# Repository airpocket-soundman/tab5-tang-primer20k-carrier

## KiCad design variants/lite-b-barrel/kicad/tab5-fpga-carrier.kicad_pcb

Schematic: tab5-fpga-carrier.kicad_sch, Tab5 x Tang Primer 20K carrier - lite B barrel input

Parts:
C1: 100u/35V; CP_Elec_6.3x7.7; LCSC C2983388
C3: 10n; C_0603_1608Metric; LCSC C57112
C4, C5: 10u/50V; C_1206_3216Metric; LCSC C13585
C6: 100n/50V; C_0603_1608Metric; LCSC C14663
C7: 220u/10V POSCAP; CP_EIA-7343-40_Kemet-Y; LCSC C242173
C8, C9: 47u/10V; C_1206_3216Metric; LCSC C96123; not fitted
C10: 10u/16V; C_1206_3216Metric; LCSC C13585
C11: 22u/10V; C_1206_3216Metric; LCSC C12891
C12, C13, C14, C15, C16, C17, C18, C19: 100n; C_0402_1005Metric; LCSC C1525
C20, C21, C22, C23, C24: 100n; C_0603_1608Metric; LCSC C14663
D1, D4: SS54; D_SMA; LCSC C22452
D3: SMBJ15A; D_SMB; LCSC C699013
D5, D6, D7, D8: LED; LED_0603_1608Metric; LCSC C2286
F1: PTC 3A hold; Fuse_1812_4532Metric; LCSC C47002391
F2: PTC 500mA; Fuse_1206_3216Metric; LCSC C315893
H3, H4, H5, H6: M3; MountingHole_3.2mm_M3
J1: DC 12V ONLY; BarrelJack_Horizontal
J3: M5-BUS (to Tab5); PinHeader_2x15_Tab5_Bottom
J4: SOCKET XDAP-4042044-20401; DDR3_XDAP_4042044_20401; LCSC C22471982
J5: HDMI OUT; HDMI_A_Molex_208658-1001_Horizontal
J6: PMOD1; PinHeader_2x06_P2.54mm_Vertical; not fitted
J7: PMOD2; PinHeader_2x06_P2.54mm_Vertical; not fitted
J8: GPIO pads; PinHeader_1x09_P2.54mm_Vertical; not fitted
JP1: BUS ARM (open by default); PinHeader_1x02_P2.54mm_Vertical
L1: 15u MS1040-150M; L_COILMX_MS1040; LCSC C380054
Q1, Q2, Q3, Q4: 2N7002; SOT-23; LCSC C8545
Q5: MMBT3904; SOT-23; LCSC C20526
R6, R36, R37, R52: 10k; R_0603_1608Metric; LCSC C25804
R7: 3.3k; R_0603_1608Metric; LCSC C22978
R8, R41, R47, R48, R49, R50: 100k; R_0603_1608Metric; LCSC C25803
R9: 15k; R_0603_1608Metric; LCSC C22809
R10, R11, R12, R13, R14, R15, R16, R19, R20, R21, R22, R23, R24, R26, R27: 680R; R_0603_1608Metric; LCSC C23228
R17, R18, R25: 0R; R_0603_1608Metric; LCSC C21189; not fitted
R28, R29, R32, R33, R34, R35: 510R; R_0603_1608Metric; LCSC C23193
R30, R31: 510R; R_0402_1005Metric; LCSC C25123
R38, R39: 2.2k; R_0603_1608Metric; LCSC C4190
R40, R51: 47k; R_0603_1608Metric; LCSC C25819
R42, R43, R44, R45: 1k; R_0603_1608Metric; LCSC C21190
R46: 22k; R_0603_1608Metric; LCSC C31850
SW1: SW; SW_SPST_EVQP0
SW2: RESET (Tab5); SW_SPST_EVQP0
SW3: FPGA ON/OFF; SW_DIP_SPSTx01_Slide_9.78x4.72mm_W7.62mm_P2.54mm
U2: TPS5430DDAR; TI_SO-PowerPAD-8_ThermalVias; LCSC C9864
U3: XC6206P332MR-G; SOT-23; LCSC C5446
U4, U5, U6: RCLAMP0524P; DFN2510-10L_RCLAMP0524P; LCSC C293965
U7, U8: SN74CB3Q3245PWR; TSSOP-20_4.4x6.5mm_P0.65mm; LCSC C470961
U9: TPS3839G33DBZR; SOT-23; LCSC C485802
U10: TPS3839K50DBZR; SOT-23; LCSC C702204

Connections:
+3V3: C11.1, C20.1, C21.1, J6.11, J6.12, J7.11, J7.12, J8.1, Q1.1 (G), Q2.1 (G), R36.1, R37.1, R46.1, R51.1, U3.2 (VO), U7.20 (VCC), U8.20 (VCC)
+5V: C7.1, C8.1, C9.1, C10.1, C23.1, F2.1, J4.4 (+5V), J4.5 (+5V), J4.6 (+5V), J4.7 (+5V), L1.2, R6.1, U3.3 (VI), U10.3 (VDD)
BUCK_BOOT: C3.1, U2.1 (BOOT)
BUCK_EN: R8.2, R9.1, SW3.1, U2.5 (EN)
BUCK_FB: R6.2, R7.1, R49.1, U2.4 (VSENSE)
BUCK_PH: C3.2, D4.1 (K), L1.1, U2.8 (PH)
BUS_ARM: JP1.2, Q3.1 (G), R47.1
BUS_OE_MID: Q3.2 (S), Q4.3 (D)
BUS_OE_N: Q3.3 (D), R46.2, U7.19 (~OE), U8.19 (~OE)
CORE_PGOOD: Q4.1 (G), R48.1, U10.2 (~RESET)
DC_IN: D1.2 (A), F1.2
DC_RAW: F1.1, J1.1
FB_TRIM: R49.2, R50.1
F_AUX0: J4.73 (F_AUX0), R11.2
F_AUX1: J4.79 (F_AUX1), R14.2
F_AUX2: J4.95 (F_AUX2), R19.2
F_AUX3: J4.97 (F_AUX3), R20.2
F_BTN0: J4.74 (F_BTN0), SW1.1
F_CLK: J4.52 (F_CLK), R10.2
F_D0: J4.77 (F_D0), R13.2
F_D1: J4.83 (F_D1), R15.2
F_D2: J4.85 (F_D2), R16.2
F_D3: J4.103 (F_D3), R22.2
F_D4: J4.101 (F_D4), R21.2
F_D5: J4.109 (F_D5), R24.2
F_D6: J4.107 (F_D6), R23.2
F_D7: J4.115 (F_D7), R26.2
F_DIR: J4.119 (F_DIR), R27.2
F_EXT35: J4.113 (F_EXT35), R25.2
F_EXT37: J4.89 (F_EXT37), R17.2
F_EXT38: J4.91 (F_EXT38), R18.2
F_HPD: J4.30 (F_HPD), R52.2
F_HSCL: J4.36 (F_HSCL), Q1.2 (S), R36.2
F_HSDA: J4.34 (F_HSDA), Q2.2 (S), R37.2
F_LED0: J4.146 (F_LED0), R42.1
F_LED1: J4.148 (F_LED1), R43.1
F_LED2: J4.152 (F_LED2), R44.1
F_LED3: J4.154 (F_LED3), R45.1
F_RDY: J4.75 (F_RDY), R12.2
GND: C1.2, C4.2, C5.2, C6.2, C7.2, C8.2, C9.2, C10.2, C11.2, C20.2, C21.2, C22.2, C23.2, C24.2, D3.2 (A2), D4.2 (A), D5.1 (K), D6.1 (K), D7.1 (K), D8.1 (K), J1.2, J1.3, J3.1, J3.3, J3.5, J4.2 (GND), J4.3 (GND), J4.8 (GND), J4.9 (GND), J4.13 (GND), J4.14 (GND), J4.19 (GND), J4.20 (GND), J4.25 (GND), J4.26 (GND), J4.31 (GND), J4.32 (GND), J4.37 (GND), J4.38 (GND), J4.43 (GND), J4.48 (GND), J4.49 (GND), J4.54 (GND), J4.55 (GND), J4.60 (GND), J4.61 (GND), J4.66 (GND), J4.71 (GND), J4.72 (GND), J4.127 (GND), J4.128 (GND), J4.133 (GND), J4.134 (GND), J4.138 (GND), J4.139 (GND), J4.144 (GND), J4.145 (GND), J4.150 (GND), J4.151 (GND), J4.155 (GND), J4.156 (GND), J4.161 (GND), J4.162 (GND), J4.168 (GND), J4.172 (GND), J4.173 (GND), J4.178 (GND), J4.179 (GND), J4.184 (GND), J4.185 (GND), J4.189 (GND), J4.190 (GND), J4.195 (GND), J4.196 (GND), J4.MP, J5.2 (D2S), J5.5 (D1S), J5.8 (D0S), J5.11 (CKS), J5.17 (GND), J5.SH, J6.9, J6.10, J7.9, J7.10, J8.2, Q4.2 (S), Q5.2 (E), R7.2, R9.2, R28.2, R29.2, R30.2, R31.2, R32.2, R33.2, R34.2, R35.2, R41.2, R47.2, R48.2, R50.2, SW1.2, SW2.2, SW3.2, U2.6 (GND), U2.9 (GNDPAD), U3.1 (GND), U4.3 (GND), U4.8 (GND), U5.3 (GND), U5.8 (GND), U6.3 (GND), U6.8 (GND), U7.10 (GND), U8.10 (GND), U9.1 (GND), U10.1 (GND)
GPIO0: J4.125 (GPIO0), J8.3
GPIO1: J4.129 (GPIO1), J8.4
GPIO2: J4.131 (GPIO2), J8.5
GPIO3: J4.176 (GPIO3), J8.6
GPIO4: J4.180 (GPIO4), J8.7
GPIO5: J4.182 (GPIO5), J8.8
GPIO6: J4.186 (GPIO6), J8.9
HDMI_5V: F2.2, J5.18 (+5V), R38.1, R39.1, U6.2 (IO2), U6.9 (NC)
HDMI_CKN: C19.1, J4.142 (HDMI_CKN)
HDMI_CKN_C: C19.2, J5.12 (CK-), R35.1, U5.5 (IO4), U5.6 (NC)
HDMI_CKP: C18.1, J4.140 (HDMI_CKP)
HDMI_CKP_C: C18.2, J5.10 (CK+), R34.1, U5.4 (IO3), U5.7 (NC)
HDMI_D0N: C17.1, J4.132 (HDMI_D0N)
HDMI_D0N_C: C17.2, J5.9 (D0-), R33.1, U5.2 (IO2), U5.9 (NC)
HDMI_D0P: C16.1, J4.130 (HDMI_D0P)
HDMI_D0P_C: C16.2, J5.7 (D0+), R32.1, U5.1 (IO1), U5.10 (NC)
HDMI_D1N: C15.1, J4.70 (HDMI_D1N)
HDMI_D1N_C: C15.2, J5.6 (D1-), R31.1, U4.5 (IO4), U4.6 (NC)
HDMI_D1P: C14.1, J4.68 (HDMI_D1P)
HDMI_D1P_C: C14.2, J5.4 (D1+), R30.1, U4.4 (IO3), U4.7 (NC)
HDMI_D2N: C13.1, J4.58 (HDMI_D2N)
HDMI_D2N_C: C13.2, J5.3 (D2-), R29.1, U4.2 (IO2), U4.9 (NC)
HDMI_D2P: C12.1, J4.56 (HDMI_D2P)
HDMI_D2P_C: C12.2, J5.1 (D2+), R28.1, U4.1 (IO1), U4.10 (NC)
HDMI_HPD: J5.19 (HPD), R40.1, U6.5 (IO4), U6.6 (NC)
HDMI_SCL: J5.15 (SCL), Q1.3 (D), R38.2, U6.4 (IO3), U6.7 (NC)
HDMI_SDA: J5.16 (SDA), Q2.3 (D), R39.2, U6.1 (IO1), U6.10 (NC)
HPD_B: Q5.1 (B), R40.2, R41.1
HPD_BUF: C24.1, Q5.3 (C), R51.2, R52.1
ISO_AUX0: R11.1, U7.17 (B2)
ISO_AUX1: R14.1, U7.14 (B5)
ISO_AUX2: R19.1, U7.11 (B8)
ISO_AUX3: R20.1, U8.18 (B1)
ISO_CLK: R10.1, U7.18 (B1)
ISO_D0: R13.1, U7.15 (B4)
ISO_D1: R15.1, U7.13 (B6)
ISO_D2: R16.1, U7.12 (B7)
ISO_D3: R22.1, U8.16 (B3)
ISO_D4: R21.1, U8.17 (B2)
ISO_D5: R24.1, U8.14 (B5)
ISO_D6: R23.1, U8.15 (B4)
ISO_D7: R26.1, U8.13 (B6)
ISO_DIR: R27.1, U8.12 (B7)
ISO_RDY: R12.1, U7.16 (B3)
LED0_A: D5.2 (A), R42.2
LED1_A: D6.2 (A), R43.2
LED2_A: D7.2 (A), R44.2
LED3_A: D8.2 (A), R45.2
M_AUX0: J3.4, U7.3 (A2)
M_AUX1: J3.10, U7.6 (A5)
M_AUX2: J3.16, U7.9 (A8)
M_AUX3: J3.15, U8.2 (A1)
M_CLK: J3.2, U7.2 (A1)
M_D0: J3.7, U7.5 (A4)
M_D1: J3.9, U7.7 (A6)
M_D2: J3.11, U7.8 (A7)
M_D3: J3.19, U8.4 (A3)
M_D4: J3.20, U8.3 (A2)
M_D5: J3.21, U8.6 (A5)
M_D6: J3.22, U8.5 (A4)
M_D7: J3.23, U8.7 (A6)
M_DIR: J3.26, U8.8 (A7)
M_EXT35: J3.24, R25.1
M_EXT37: J3.14, R17.1
M_EXT38: J3.13, R18.1
M_RDY: J3.8, U7.4 (A3)
P1_0: J4.76 (P1_0), J6.1
P1_1: J4.84 (P1_1), J6.3
P1_2: J4.90 (P1_2), J6.5
P1_3: J4.121 (P1_3), J6.7
P1_4: J4.78 (P1_4), J6.2
P1_5: J4.86 (P1_5), J6.4
P1_6: J4.92 (P1_6), J6.6
P1_7: J4.123 (P1_7), J6.8
P2_0: J4.40 (P2_0), J7.1
P2_1: J4.44 (P2_1), J7.3
P2_2: J4.50 (P2_2), J7.5
P2_3: J4.62 (P2_3), J7.7
P2_4: J4.42 (P2_4), J7.2
P2_5: J4.46 (P2_5), J7.4
P2_6: J4.80 (P2_6), J7.6
P2_7: J4.64 (P2_7), J7.8
TAB_3V3: C22.1, J3.12, U9.3 (VDD)
TAB_PGOOD: JP1.1, U9.2 (~RESET)
TAB_RST: J3.6, SW2.1
TAB_SCL: J3.18
TAB_SDA: J3.17
VIN: C1.1, C4.1, C5.1, C6.1, D1.1 (K), D3.1 (A1), J3.25, J3.27, J3.29, R8.1, U2.7 (VIN)

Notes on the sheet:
POWER INPUT: DC barrel + USB-C PD (OR) -> VIN
USB-C PD sink (CH224K, 12V request)
VIN -> +5V buck (TPS5430)
+5V -> +3V3 local logic only, no external loads
M5-BUS header (Tab5-facing side)
Power-off bus isolation + 33R (M=Tab5, ISO=switch, F=FPGA)
HDMI OUT connector + DDC/HPD level shift + ESD
HDMI TMDS 510R Basic bias, ESD
HDMI TMDS AC coupling caps
PMOD x2
FPGA JTAG header
Spare FPGA I/O pads
LEDs / buttons
Mounting holes (Tab5 M3)
Tang Primer 20K Core SODIMM socket (pin names = nets)
Nets: GND +5V +3V3 are power symbols; all other nets connect by label.
M5-Bus pins 28 (5V) and 30 (BAT) are intentionally NOT connected (Tab5 outputs).
Do NOT tie Tab5 5V to the FPGA 5V rail. GND is common.

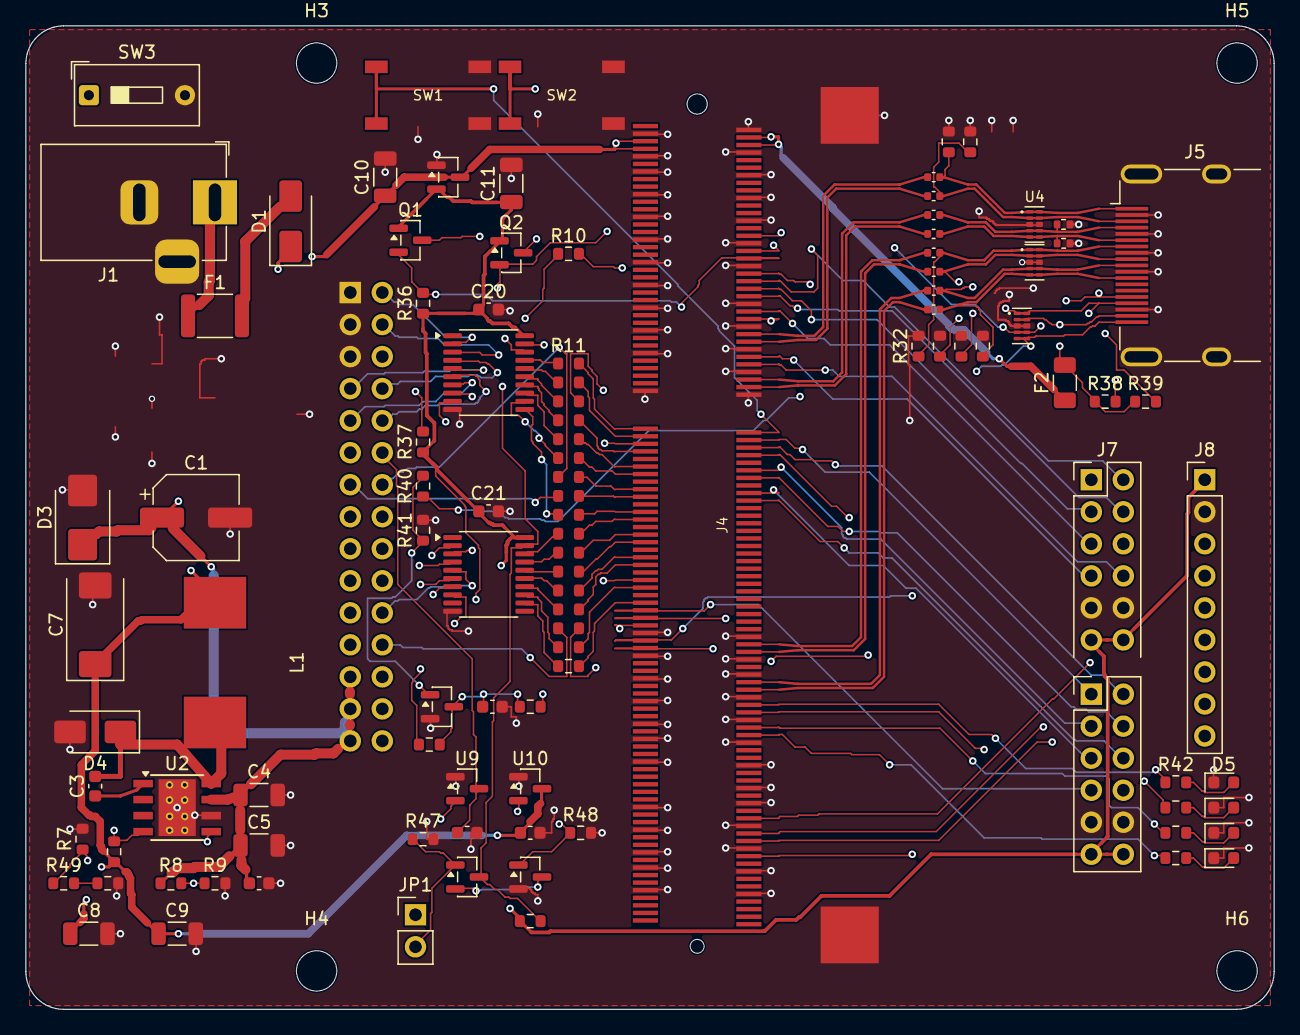
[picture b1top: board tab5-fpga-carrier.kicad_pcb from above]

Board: 4 copper layers, 99.0 x 78.0 mm, 109 parts (1 on the bottom side), 126 nets.

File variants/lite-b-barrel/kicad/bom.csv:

Refs,Value,Footprint,Qty,DNP,LCSC,JLC class,Note
J1,DC 12V ONLY,Connector_BarrelJack:BarrelJack_Horizontal,1,,,THT/hand-solder or extended (select part),"DC barrel jack, centre positive (THT, hand assembly)"
F1,PTC 3A hold,Fuse:Fuse_1812_4532Metric,1,,C47002391,selected (verify stock at order),
"D1,D4",SS54,Diode_SMD:D_SMA,2,,C22452,selected (verify stock at order),reverse-polarity + OR (DC jack)
D3,SMBJ15A,Diode_SMD:D_SMB,1,,C699013,selected (verify stock at order),"YANGJIE 15V standoff, 24.4V specified clamp; regulated 12V PoC input only"
C1,100u/35V,Capacitor_SMD:CP_Elec_6.3x7.7,1,,C2983388,selected (verify stock at order),
U2,TPS5430DDAR,Package_SO:TI_SO-PowerPAD-8_ThermalVias,1,,C9864,selected (verify stock at order),
C3,10n,Capacitor_SMD:C_0603_1608Metric,1,,C57112,selected (verify stock at order),
L1,15u MS1040-150M,carrier:L_COILMX_MS1040,1,,C380054,selected (verify stock at order),
"R36,R37,R52,R6",10k,Resistor_SMD:R_0603_1608Metric,4,,C25804,selected (verify stock at order),
R7,3.3k,Resistor_SMD:R_0603_1608Metric,1,,C22978,selected (verify stock at order),"3.3k parallel (100k+100k): Req 3246.433 ohm, nominal buck 4.982V"
"R41,R47,R48,R49,R50,R8",100k,Resistor_SMD:R_0603_1608Metric,6,,C25803,selected (verify stock at order),
R9,15k,Resistor_SMD:R_0603_1608Metric,1,,C22809,selected (verify stock at order),External EN divider ~9.4V threshold; stays off at default USB 5V/9V
"C4,C5",10u/50V,Capacitor_SMD:C_1206_3216Metric,2,,C13585,selected (verify stock at order),
C6,100n/50V,Capacitor_SMD:C_0603_1608Metric,1,,C14663,selected (verify stock at order),
C7,220u/10V POSCAP,Capacitor_Tantalum_SMD:CP_EIA-7343-40_Kemet-Y,1,,C242173,selected (verify stock at order),"Panasonic 10TPB220M, 220uF 10V ESR max40mohm; TI reference output capacitor"
"C8,C9",47u/10V,Capacitor_SMD:C_1206_3216Metric,2,DNP,C96123,selected (verify stock at order),
U3,XC6206P332MR-G,Package_TO_SOT_SMD:SOT-23,1,,C5446,selected (verify stock at order),3.3V local logic only; no external 3V3 loads; design limit 50mA
C10,10u/16V,Capacitor_SMD:C_1206_3216Metric,1,,C13585,selected (verify stock at order),
C11,22u/10V,Capacitor_SMD:C_1206_3216Metric,1,,C12891,selected (verify stock at order),
J3,M5-BUS (to Tab5),carrier:PinHeader_2x15_Tab5_Bottom,1,,,THT/hand-solder or extended (select part),"User confirmed 2026-10-24: rear view, battery left, pin1 GND on left; mirrored-column footprint"
"R10,R11,R12,R13,R14,R15,R16,R19,R20,R21,R22,R23,R24,R26,R27",680R,Resistor_SMD:R_0603_1608Metric,15,,C23228,selected (verify stock at order),"PoC 1MHz, 680ohm series damping; >=250ns DATA setup/hold, weak drive/SLOW; qualified distributed-RLC sensitivity"
"R17,R18,R25",0R,Resistor_SMD:R_0603_1608Metric,3,DNP,C21189,selected (verify stock at order),16-bit extension (DNP): connects G37 to FPGA
J4,SOCKET XDAP-4042044-20401,carrier:DDR3_XDAP_4042044_20401,1,,C22471982,selected (verify stock at order),"PCBA required; socket only, user supplies Tang Primer 20K Core module"
J5,HDMI OUT,Connector_Video:HDMI_A_Molex_208658-1001_Horizontal,1,,,THT/hand-solder or extended (select part),"TMDS from FPGA true-LVDS outputs (3.3V bank), AC coupled + 499R bias + ESD (official-Dock style)"
"C12,C13,C14,C15,C16,C17,C18,C19",100n,Capacitor_SMD:C_0402_1005Metric,8,,C1525,selected (verify stock at order),100nF AC coupling; low-profile 0402 under Core
"R28,R29,R32,R33,R34,R35",510R,Resistor_SMD:R_0603_1608Metric,6,,C23193,selected (verify stock at order),Basic 510 ohm; +2.2% vs 499; unchanged HDMI branch geometry
"R30,R31",510R,Resistor_SMD:R_0402_1005Metric,2,,C25123,selected (verify stock at order),Basic 510 ohm; +2.2% vs 499; unchanged HDMI branch geometry
"U4,U5,U6",RCLAMP0524P,carrier:DFN2510-10L_RCLAMP0524P,3,,C293965,selected (verify stock at order),"TMDS ESD array (DOWO DFN2510-10L): I/O 1,2,4,5, GND 3,8; the line is routed as continuous copper through strapped pads"
F2,PTC 500mA,Fuse:Fuse_1206_3216Metric,1,,C315893,selected (verify stock at order),
"Q1,Q2,Q3,Q4",2N7002,Package_TO_SOT_SMD:SOT-23,4,,C8545,selected (verify stock at order),DDC level shifter (pin1=G pin2=S pin3=D)
"R38,R39",2.2k,Resistor_SMD:R_0603_1608Metric,2,,C4190,selected (verify stock at order),
"R40,R51",47k,Resistor_SMD:R_0603_1608Metric,2,,C25819,selected (verify stock at order),
J6,PMOD1,Connector_PinHeader_2.54mm:PinHeader_2x06_P2.54mm_Vertical,1,DNP,,THT/hand-solder or extended (select part),"2x6 PMOD-style, 3.3V. Pads only: pin header is hand-fitted later (DNP)"
J7,PMOD2,Connector_PinHeader_2.54mm:PinHeader_2x06_P2.54mm_Vertical,1,DNP,,THT/hand-solder or extended (select part),"2x6 PMOD-style, 3.3V. Pads only: pin header is hand-fitted later (DNP)"
"R42,R43,R44,R45",1k,Resistor_SMD:R_0603_1608Metric,4,,C21190,selected (verify stock at order),
"D5,D6,D7,D8",LED,LED_SMD:LED_0603_1608Metric,4,,C2286,selected (verify stock at order),
SW1,SW,Button_Switch_SMD:SW_SPST_EVQP0,1,,,THT/hand-solder or extended (select part),
SW2,RESET (Tab5),Button_Switch_SMD:SW_SPST_EVQP0,1,,,THT/hand-solder or extended (select part),pulls the M5-Bus RST/EN line (pin 6) low: resets the ESP32-P4
SW3,FPGA ON/OFF,Button_Switch_THT:SW_DIP_SPSTx01_Slide_9.78x4.72mm_W7.62mm_P2.54mm,1,,,THT/hand-solder or extended (select part),"slide switch: ON = open (buck runs), OFF = short EN to GND (FPGA 5V off). Tab5 keeps its own power button. Sits in the switch row with the two tact switches, clear of the board edge"
J8,GPIO pads,Connector_PinHeader_2.54mm:PinHeader_1x09_P2.54mm_Vertical,1,DNP,,THT/hand-solder or extended (select part),"spare FPGA I/O (3.3V, bank 7): pads only, hand-fit a header or wires later"
"H3,H4,H5,H6",M3,MountingHole:MountingHole_3.2mm_M3,4,,,THT/hand-solder or extended (select part),
"U7,U8",SN74CB3Q3245PWR,Package_SO:TSSOP-20_4.4x6.5mm_P0.65mm,2,,C470961,selected (verify stock at order),Ioff protected 8-bit passive bus switch; OE pulled high by default
"C20,C21,C22,C23,C24",100n,Capacitor_SMD:C_0603_1608Metric,5,,C14663,selected (verify stock at order),
U9,TPS3839G33DBZR,Package_TO_SOT_SMD:SOT-23,1,,C485802,selected (verify stock at order),"3.08V / 4.38V supervisor, 200ms typical release delay"
U10,TPS3839K50DBZR,Package_TO_SOT_SMD:SOT-23,1,,C702204,selected (verify stock at order),"3.08V / 4.38V supervisor, 200ms typical release delay"
JP1,BUS ARM (open by default),Connector_PinHeader_2.54mm:PinHeader_1x02_P2.54mm_Vertical,1,,,THT/hand-solder or extended (select part),Fit shunt only after firmware GPIO ownership has been checked
R46,22k,Resistor_SMD:R_0603_1608Metric,1,,C31850,selected (verify stock at order),
Q5,MMBT3904,Package_TO_SOT_SMD:SOT-23,1,,C20526,selected (verify stock at order),"Active-low HPD; input only, invert and debounce >=10ms; R52 limits off-bank charge injection, no hotplug guarantee"

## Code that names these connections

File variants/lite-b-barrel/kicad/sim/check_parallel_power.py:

"""Check minimum-success parallel link and power topology on the actual PCB.
KiCad Python; CHECK_PCB / CHECK_JSON support isolated fault-injection tests.
No claim of physical DMA, DDR3 or timing validation is made by this checker.
"""
import json
import os
from pathlib import Path
import pcbnew

HERE=Path(__file__).resolve().parent
# Independently reviewed against M5Stack and Sipeed connector drawings.
MBUS={'D0':7,'D1':9,'D2':11,'D3':19,'D4':20,'D5':21,'D6':22,'D7':23,
      'CLK':2,'RDY':8,'DIR':26,'AUX0':4,'AUX1':10,'AUX2':16,'AUX3':15}
CORE={'D0':77,'D1':83,'D2':85,'D3':103,'D4':101,'D5':109,'D6':107,'D7':115,
      'CLK':52,'RDY':75,'DIR':119,'AUX0':73,'AUX1':79,'AUX2':95,'AUX3':97}


def check(board):
    fps={fp.GetReference():fp for fp in board.GetFootprints()}
    conn=board.GetConnectivity()
    def pads(ref):return {p.GetNumber():p for p in fps[ref].Pads()}
    def reaches(a,b):
        if a.GetNetname()!=b.GetNetname():return False
        stack=[a];seen=set()
        while stack:
            t=stack.pop();uid=t.m_Uuid.AsString()
            if uid in seen:continue
            seen.add(uid)
            if uid==b.m_Uuid.AsString():return True
            stack.extend(t for t in conn.GetConnectedItems(t,getattr(pcbnew,'EXCLUDE_ZONES',0)) if t.GetNetname()==a.GetNetname())
        return False
    def pin_net(ref,num,net):return pads(ref)[str(num)].GetNetname()==net
    checks=[]
    def record(name,ok,**kw):checks.append(dict(name=name,ok=bool(ok),**kw))
    # User checked the real Tab5 rear face, battery compartment on the left.
    def at(ref,num,x,y):
        p=pads(ref)[str(num)].GetPosition()
        return abs(pcbnew.ToMM(p.x)-x)<.003 and abs(pcbnew.ToMM(p.y)-y)<.003
    record('M5Bus_confirmed_left_pin1',fps['J3'].IsFlipped() and all(at('J3',n,x,y) for n,x,y in [(1,53.73,22.15),(2,56.27,22.15),(3,53.73,24.69),(29,53.73,57.71),(30,56.27,57.71)]))
    for sig,host_pin in MBUS.items():
        a=pads('J3')[str(host_pin)];c=pads('J4')[str(CORE[sig])]
        switches=[(f,p) for f in ('U7','U8') for n,p in pads(f).items() if n in [str(i) for i in range(2,10)] and p.GetNetname()=='M_'+sig]
        resistors=[fp for fp in fps.values() if fp.GetReference().startswith('R') and any(p.GetNetname()=='ISO_'+sig for p in fp.Pads())]
        ok=len(switches)==1 and len(resistors)==1
        if ok:
            ref,sw_a=switches[0];sw_b=pads(ref)[str(20-int(sw_a.GetNumber()))]
            resistor=resistors[0];rp={p.GetNumber():p for p in resistor.Pads()}
            ok=(fps[ref].GetValue()=='SN74CB3Q3245PWR' and resistor.GetValue()=='680R' and
                a.GetNetname()=='M_'+sig and c.GetNetname()=='F_'+sig and
                sw_b.GetNetname()=='ISO_'+sig and rp['1'].GetNetname()=='ISO_'+sig and
                rp['2'].GetNetname()=='F_'+sig and reaches(a,sw_a) and reaches(sw_b,rp['1']) and reaches(rp['2'],c))
        record('parallel_'+sig,ok,mbus_pin=host_pin,core_pin=CORE[sig])
    for ref in ('U7','U8'):
        record(ref+'_power_isolation',all(pin_net(ref,n,v) for n,v in [(10,'GND'),(19,'BUS_OE_N'),(20,'+3V3')]))
    record('OE_default_high',fps['R46'].GetValue()=='22k' and pin_net('R46',1,'+3V3') and pin_net('R46',2,'BUS_OE_N'))
    record('manual_arm_default_open',pin_net('JP1',1,'TAB_PGOOD') and pin_net('JP1',2,'BUS_ARM') and pin_net('R47',1,'BUS_ARM') and pin_net('R47',2,'GND'))
    record('OE_series_MOSFET_AND',all(pin_net(r,n,v) for r,n,v in [('Q3',1,'BUS_ARM'),('Q3',2,'BUS_OE_MID'),('Q3',3,'BUS_OE_N'),('Q4',1,'CORE_PGOOD'),('Q4',2,'GND'),('Q4',3,'BUS_OE_MID')]))
    record('both_supplies_monitored',fps['U9'].GetValue()=='TPS3839G33DBZR' and fps['U10'].GetValue()=='TPS3839K50DBZR' and all(pin_net(r,n,v) for r,n,v in [('U9',3,'TAB_3V3'),('U9',2,'TAB_PGOOD'),('U10',3,'+5V'),('U10',2,'CORE_PGOOD')]))
    record('Tab5_5V_and_BAT_not_tied',not pads('J3')['28'].GetNetname() and not pads('J3')['30'].GetNetname())
    ground_pins=(2,3,8,9,13,14,19,20,25,26,31,32,37,38,43,48,49,54,55,60,61,66,71,72,127,128,133,134,138,139,144,145,150,151,155,156,161,162,168,172,173,178,179,184,185,189,190,195,196)
    record('shared_ground_returns',all(pin_net('J4',n,'GND') for n in ground_pins) and all(pin_net('J3',n,'GND') for n in (1,3,5)))
    record('Core_5V_pins',all(pin_net('J4',n,'+5V') for n in (4,5,6,7)))
    record('Tab5_HVIN_pins',all(pin_net('J3',n,'VIN') for n in (25,27,29)))
    record('barrel_only_no_PD',not any(r in fps for r in ('J2','U1','C2','R1','R2','R3','R4','R5','D2')) and pin_net('J1',1,'DC_RAW') and pin_net('F1',1,'DC_RAW') and pin_net('F1',2,'DC_IN') and pin_net('D1',2,'DC_IN') and pin_net('D1',1,'VIN'))
    record('regulated_5V_parts',fps['U2'].GetValue()=='TPS5430DDAR' and fps['R6'].GetValue()=='10k' and fps['R7'].GetValue()=='3.3k' and fps['R49'].GetValue()=='100k' and fps['R50'].GetValue()=='100k' and all(pin_net(r,n,v) for r,n,v in [('R7',1,'BUCK_FB'),('R7',2,'GND'),('R49',1,'BUCK_FB'),('R49',2,'FB_TRIM'),('R50',1,'FB_TRIM'),('R50',2,'GND')]) and fps['C7'].GetValue()=='220u/10V POSCAP' and fps['C8'].IsDNP() and fps['C9'].IsDNP())
    record('ceramic_stable_bus_LDO',fps['U3'].GetValue()=='XC6206P332MR-G' and all(pin_net('U3',n,v) for n,v in [(1,'GND'),(2,'+3V3'),(3,'+5V')]))
    record('replacement_socket_fitted',not fps['J4'].IsDNP() and fps['J4'].GetValue()=='SOCKET XDAP-4042044-20401')
    record('Basic_HDMI_bias_510ohm',all(fps['R'+str(n)].GetValue()=='510R' and not fps['R'+str(n)].IsDNP() for n in range(28,36)))
    record('initial_extension_unpopulated',all(fps[r].IsDNP() for r in ('R17','R18','R25')))
    for net in ('BUCK_PH','BUCK_BOOT'):
        items=[t for t in board.GetTracks() if t.GetNetname()==net]
        record(net+'_front_no_vias',all(not isinstance(t,pcbnew.PCB_VIA) and t.GetLayer()==pcbnew.F_Cu for t in items),length_mm=sum(pcbnew.ToMM(t.GetLength()) for t in items if not isinstance(t,pcbnew.PCB_VIA)))
    cases=[dict(tab_power=t,core_power=c,arm=a,enabled=bool(t and c and a)) for t in (False,True) for c in (False,True) for a in (False,True)]
    return dict(ok=all(c['ok'] for c in checks),checks=checks,power_state_logic=cases,
                note='Power-state logic is a topology check, not measured leakage or transient behavior.')


if __name__=='__main__':
    board=pcbnew.LoadBoard(os.environ.get('CHECK_PCB',str(HERE.parent/'tab5-fpga-carrier.kicad_pcb')))
    result=check(board)
    Path(os.environ.get('CHECK_JSON',str(HERE/'parallel_power_check.json'))).write_text(json.dumps(result,indent=2),encoding='utf-8')
    print('Parallel/power:',result['ok'],'checks',len(result['checks']))
    for c in result['checks']:
        if not c['ok']:print('FAIL',c['name'])
    raise SystemExit(0 if result['ok'] else 1)

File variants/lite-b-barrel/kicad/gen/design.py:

from design_variant import *

# BEGIN PoC parallel 680R qualification
_build_before_series_680 = build
def build():
    cs = _build_before_series_680()
    changed = []
    for c in cs:
        if not c.ref.startswith('R') or len(c.pins) != 2:
            continue
        nets = set(c.pins.values())
        iso = next((n for n in nets if n and n.startswith('ISO_')), None)
        if iso and nets == {iso, 'F_' + iso[4:]}:
            assert c.value in ('33R','330R','680R') and not c.dnp, (c.ref, c.value)
            c.value = '680R'
            c.lcsc = 'C23228'
            c.comment = 'PoC 1MHz, 680ohm series damping; >=250ns DATA setup/hold, weak drive/SLOW; qualified distributed-RLC sensitivity'
            changed.append(c.ref)
    assert len(changed) == 15, changed
    return cs
# END PoC parallel 680R qualification

# BEGIN qualified low-profile HDMI and isolated active-low HPD
_build_before_hdmi_revision = build
def build():
    cs=_build_before_hdmi_revision();lookup={c.ref:c for c in cs}
    for i in range(12,20):
        c=lookup['C'+str(i)];c.fp='Capacitor_SMD:C_0402_1005Metric';c.lcsc='C1525'
        c.comment='100nF AC coupling; low-profile 0402 under Core'
    u=lookup['U6'];u.sym='carrier:RCLAMP0524P';u.fp='carrier:DFN2510-10L_RCLAMP0524P';u.value='RCLAMP0524P';u.lcsc='C293965'
    u.pins={'1':'HDMI_SDA','10':'HDMI_SDA','2':'HDMI_5V','9':'HDMI_5V','4':'HDMI_SCL','7':'HDMI_SCL','5':'HDMI_HPD','6':'HDMI_HPD','3':'GND','8':'GND'}
    u.comment='Independent ground-referenced ESD channels, no shared VCC steering; NC counterpart lands externally copper strapped'
    for ref,val,lcsc,pins in [('R40','47k','C25819',{'1':'HDMI_HPD','2':'HPD_B'}),('R41','100k','C25803',{'1':'HPD_B','2':'GND'})]:
        c=lookup[ref];c.value=val;c.lcsc=lcsc;c.pins=pins
    new=[
      Comp('Q5','Transistor_BJT:MMBT3904','Package_TO_SOT_SMD:SOT-23','MMBT3904',{'1':'HPD_B','2':'GND','3':'HPD_BUF'},'hdmi',pos=(61,55),lcsc='C20526'),
      Comp('R51','Device:R',R0603,'47k',{'1':'+3V3','2':'HPD_BUF'},'hdmi',pos=(60,58),lcsc='C25819'),
      Comp('R52','Device:R',R0603,'10k',{'1':'HPD_BUF','2':'F_HPD'},'hdmi',pos=(68,55),lcsc='C25804'),
      Comp('C24','Device:C',C0603,'100n',{'1':'HPD_BUF','2':'GND'},'hdmi',pos=(65,55),lcsc='C14663')]
    for c in new:
        c.dnp=False;c.comment='Active-low HPD; input only, invert and debounce >=10ms; R52 limits off-bank charge injection, no hotplug guarantee'
    cs.extend(new);return cs
# END qualified low-profile HDMI and isolated active-low HPD

# Akizuki TS-06104 hand-solder buttons, manufacturer drawing p8.

_build_before_akizuki_buttons = build
def build():
    cs = _build_before_akizuki_buttons()
    for c in cs:
        if c.ref in ('SW1','SW2'):
            c.fp='carrier:SW_TS_06104_HandSolder';c.value='TS-06104';c.lcsc=''
            c.pos=((59.9 if c.ref=='SW1' else 70.5),6.5);c.rot=0
            c.comment='Manual assembly; Akizuki115969; TS-06104 H4.3mm; dedicated manufacturer p8 lands; pads1=A/B and2=C/D'
    return cs

_build_before_hdmi_pcba = build
def build():
    cs=_build_before_hdmi_pcba()
    c=next(c for c in cs if c.ref=='J5');c.lcsc='C916313'
    c.comment='MOLEX2086581001 PCBA mandatory including19 SMT contacts and all4 SH shell tabs; confirm supplier preview'
    return cs
